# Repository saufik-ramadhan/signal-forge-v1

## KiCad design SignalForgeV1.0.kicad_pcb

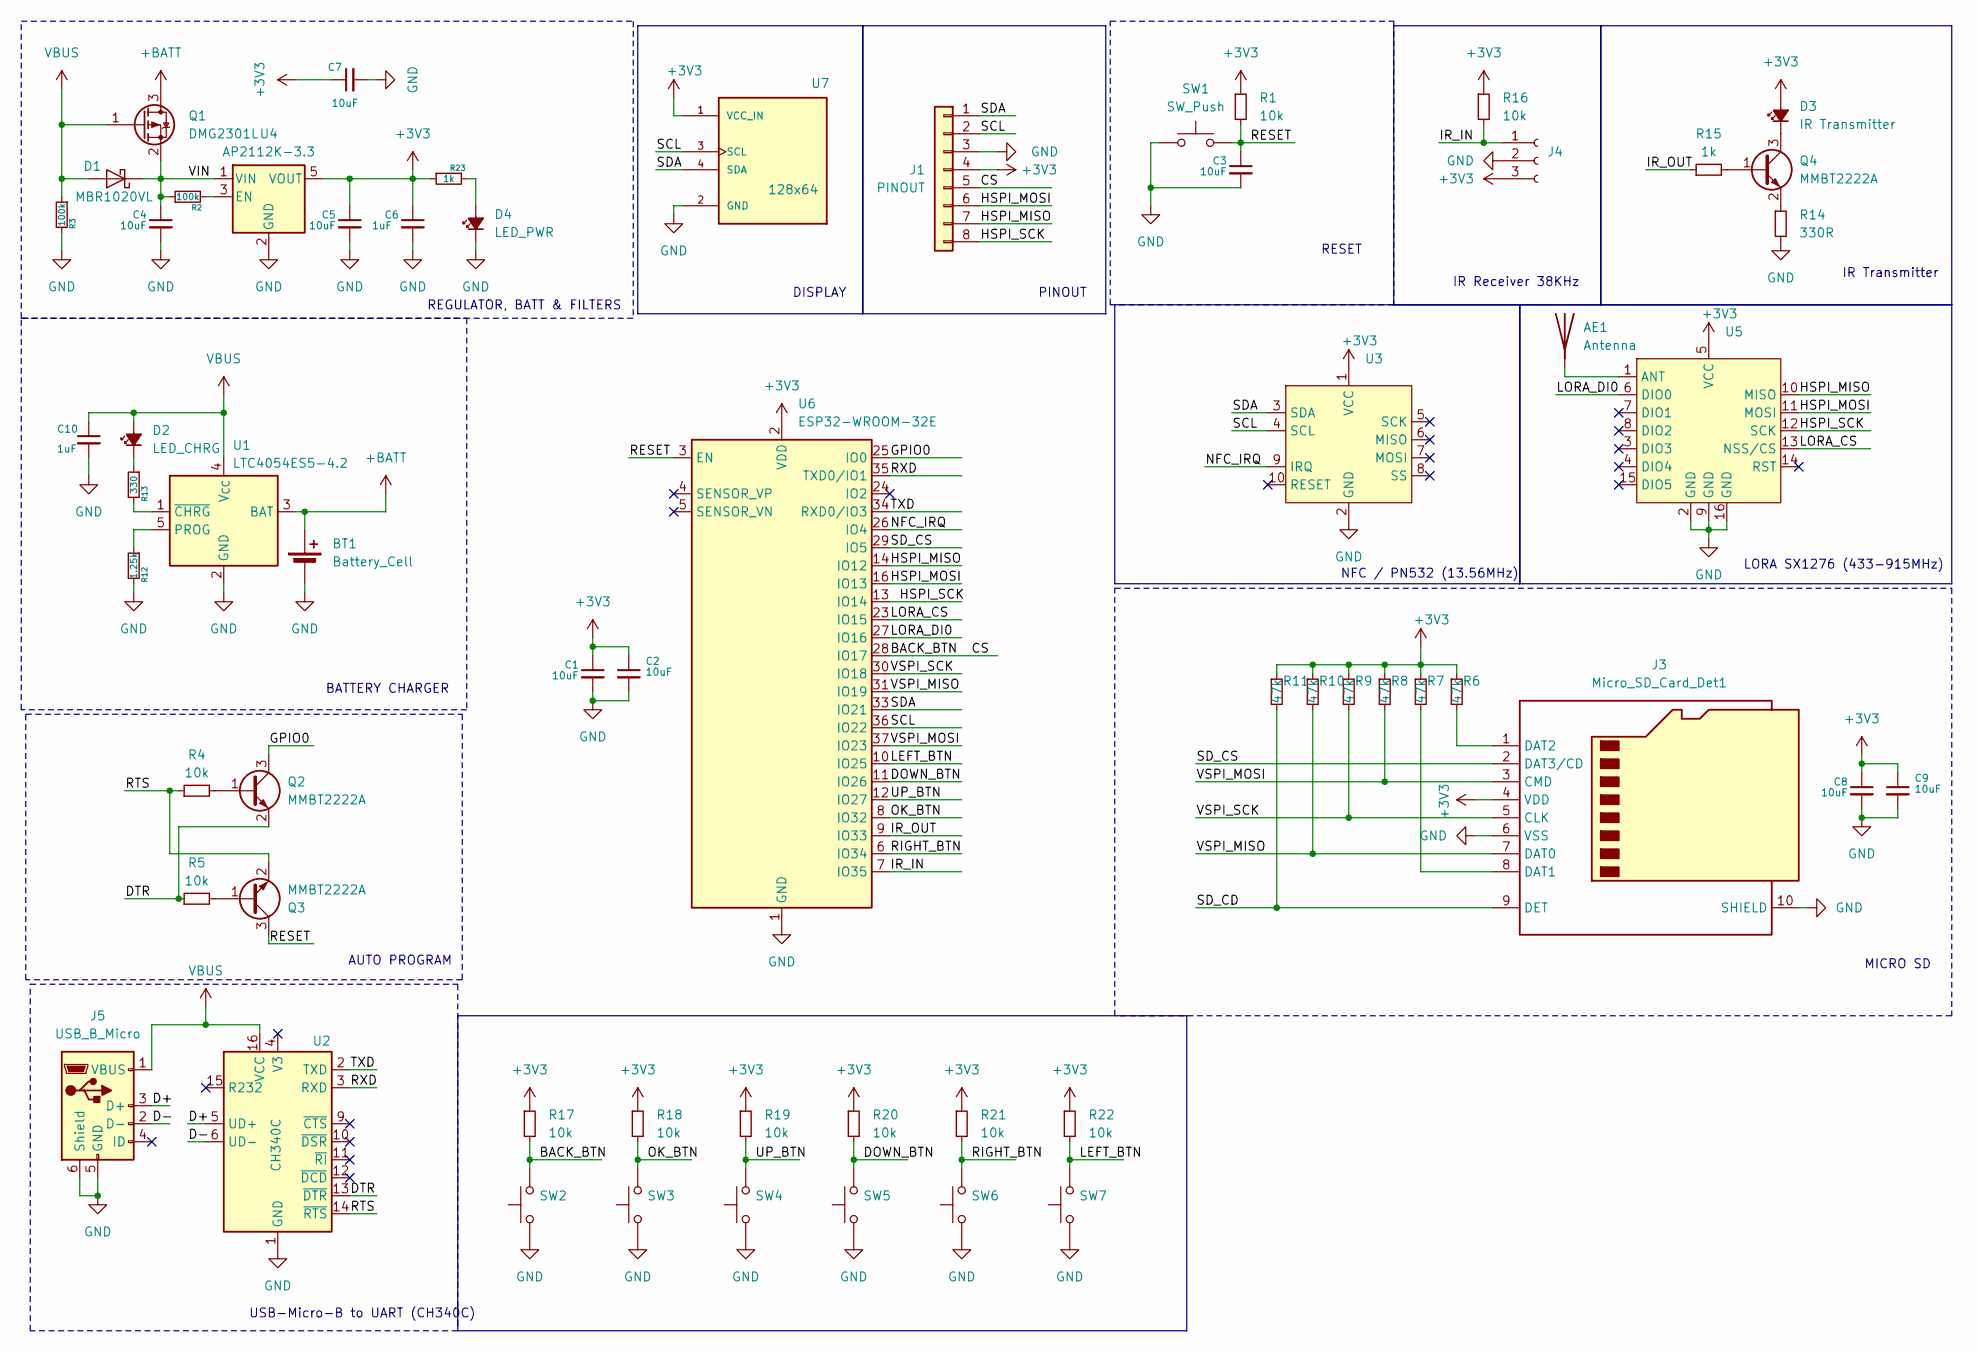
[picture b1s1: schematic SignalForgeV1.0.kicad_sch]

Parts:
AE1: Antenna; TestPoint_THTPad_D2.0mm_Drill1.0mm
BT1: Battery_Cell; JST_EH_S2B-EH_1x02_P2.50mm_Horizontal
C1, C2, C3, C4, C5, C7, C8, C9: 10uF; C_0805_2012Metric_Pad1.18x1.45mm_HandSolder
C6, C10: 1uF; C_0805_2012Metric_Pad1.18x1.45mm_HandSolder
D1: MBR1020VL; D_SOD-123F
D2: LED_CHRG; LED_0805_2012Metric_Pad1.15x1.40mm_HandSolder
D3: IR Transmitter; LED_D5.0mm_Horizontal_O1.27mm_Z3.0mm
D4: LED_PWR; LED_0805_2012Metric_Pad1.15x1.40mm_HandSolder
J1: PINOUT; PinSocket_1x08_P2.54mm_Horizontal
J3: Micro_SD_Card_Det1; J_SD_Card-micro_socket_A
J4: IR Receiver; PinHeader_1x03_P2.54mm_Vertical
J5: USB_B_Micro; USB_B_Micro_SMD-TE
Q1: DMG2301L; SOT-23
Q2, Q3, Q4: MMBT2222A; SOT-23
R1, R4, R5, R16, R17, R18, R19, R20, R21, R22: 10k; R_0805_2012Metric_Pad1.20x1.40mm_HandSolder
R2, R3: 100k; R_0805_2012Metric_Pad1.20x1.40mm_HandSolder
R6, R7, R8, R9, R10, R11: 47k; R_0805_2012Metric_Pad1.20x1.40mm_HandSolder
R12: 1.25k; R_0805_2012Metric_Pad1.20x1.40mm_HandSolder
R13: 330; R_0805_2012Metric_Pad1.20x1.40mm_HandSolder
R14: 330R; R_0805_2012Metric_Pad1.20x1.40mm_HandSolder
R15, R23: 1k; R_0805_2012Metric_Pad1.20x1.40mm_HandSolder
SW1: SW_Push; SW_SPST_EVQP7C
SW2: BACK_BTN; SW_SPST_TL3342
SW3: OK_BTN; SW_SPST_TL3342
SW4: UP_BTN; SW_SPST_TL3342
SW5: DOWN_BTN; SW_SPST_TL3342
SW6: RIGHT_BTN; SW_SPST_TL3342
SW7: LEFT_BTN; SW_SPST_TL3342
U1: LTC4054ES5-4.2; TSOT-23-5
U2: CH340C; SOIC-16_3.9x9.9mm_P1.27mm
U3: PN532_Module
U4: AP2112K-3.3; SOT-23-5_HandSoldering
U5: SX1276_Module
U6: ESP32-WROOM-32E
U7: 128x64; MODULE_DM-OLED096-636; PARTREV 2018-09-10

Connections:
+3V3: C1.1, C2.1, C5.1, C6.1, C7.1, C8.1, C9.1, D3.2 (A), J1.4, J3.4 (VDD), J4.3, R1.1, R6.1, R7.1, R8.1, R9.1, R10.1, R11.1, R16.1, R17.1, R18.1, R19.1, R20.1, R21.1, R22.1, R23.1, U3.1 (VCC), U4.5 (VOUT), U5.5 (VCC), U6.2 (VDD), U7.1 (VCC_IN)
+BATT: BT1.1 (+), Q1.3 (D), U1.3 (BAT)
/BACK_BTN: J1.5, R17.2, SW2.2, U6.28 (IO17)
/D+: J5.3 (D+), U2.5 (UD+)
/D-: J5.2 (D-), U2.6 (UD-)
/DOWN_BTN: R20.2, SW5.2, U6.11 (IO26)
/DTR: Q2.2 (E), R5.1, U2.13 (~DTR)
/GPIO0: Q2.3 (C), U6.25 (IO0)
/HSPI_MISO: J1.7, U5.10 (MISO), U6.14 (IO12)
/HSPI_MOSI: J1.6, U5.11 (MOSI), U6.16 (IO13)
/HSPI_SCK: J1.8, U5.12 (SCK), U6.13 (IO14)
/IR_IN: J4.1, R16.2, U6.7 (IO35)
/IR_OUT: R15.1, U6.9 (IO33)
/LEFT_BTN: R22.2, SW7.2, U6.10 (IO25)
/LORA_CS: U5.13 (NSS/CS), U6.23 (IO15)
/LORA_DI0: U5.6 (DIO0), U6.27 (IO16)
/NFC_IRQ: U3.9 (IRQ), U6.26 (IO4)
/OK_BTN: R18.2, SW3.2, U6.8 (IO32)
/RESET: C3.1, Q3.3 (C), R1.2, SW1.2, U6.3 (EN)
/RIGHT_BTN: R21.2, SW6.2, U6.6 (IO34)
/RTS: Q3.2 (E), R4.1, U2.14 (~RTS)
/RXD: U2.3 (RXD), U6.35 (TXD0/IO1)
/SCL: J1.2, U3.4 (SCL), U6.36 (IO22), U7.3 (SCL)
/SDA: J1.1, U3.3 (SDA), U6.33 (IO21), U7.4 (SDA)
/SD_CD: J3.9 (DET), R11.2
/SD_CS: J3.2 (DAT3/CD), U6.29 (IO5)
/TXD: U2.2 (TXD), U6.34 (RXD0/IO3)
/UP_BTN: R19.2, SW4.2, U6.12 (IO27)
/VIN: C4.1, D1.1 (K), Q1.2 (S), R2.1, U4.1 (VIN)
/VSPI_MISO: J3.7 (DAT0), R10.2, U6.31 (IO19)
/VSPI_MOSI: J3.3 (CMD), R8.2, U6.37 (IO23)
/VSPI_SCK: J3.5 (CLK), R9.2, U6.30 (IO18)
GND: BT1.2 (-), C1.2, C2.2, C3.2, C4.2, C5.2, C6.2, C7.2, C8.2, C9.2, C10.2, D4.1 (K), J1.3, J3.6 (VSS), J3.10 (SHIELD), J4.2, J5.5 (GND), J5.6 (Shield), R3.2, R12.2, R14.2, SW1.1, SW2.1, SW3.1, SW4.1, SW5.1, SW6.1, SW7.1, U1.2 (GND), U2.1 (GND), U3.2 (GND), U4.2 (GND), U5.2 (GND), U5.9 (GND), U5.16 (GND), U6.1 (GND), U6.15 (GND), U6.38 (GND), U6.39 (GND), U7.2 (GND)
unnamed: AE1.1 (A), U5.1 (ANT)
unnamed: D2.1 (K), R13.1
unnamed: D3.1 (K), Q4.3 (C)
unnamed: D4.2 (A), R23.2
unnamed: J3.8 (DAT1), R7.2
unnamed: J3.1 (DAT2), R6.2
unnamed: Q2.1 (B), R4.2
unnamed: Q3.1 (B), R5.2
unnamed: Q4.1 (B), R15.2
unnamed: Q4.2 (E), R14.1
unnamed: R12.1, U1.5 (PROG)
unnamed: R13.2, U1.1 (~CHRG)
unnamed: R2.2, U4.3 (EN)
VBUS: C10.1, D1.2 (A), D2.2 (A), J5.1 (VBUS), Q1.1 (G), R3.1, U1.4 (V_{CC}), U2.16 (VCC)

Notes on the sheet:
NFC / PN532 (13.56MHz)
RESET
PINOUT
AUTO PROGRAM
BATTERY CHARGER
LORA SX1276 (433-915MHz)
IR Transmitter
USB-Micro-B to UART (CH340C)
IR Receiver 38KHz
REGULATOR, BATT & FILTERS
MICRO SD
DISPLAY

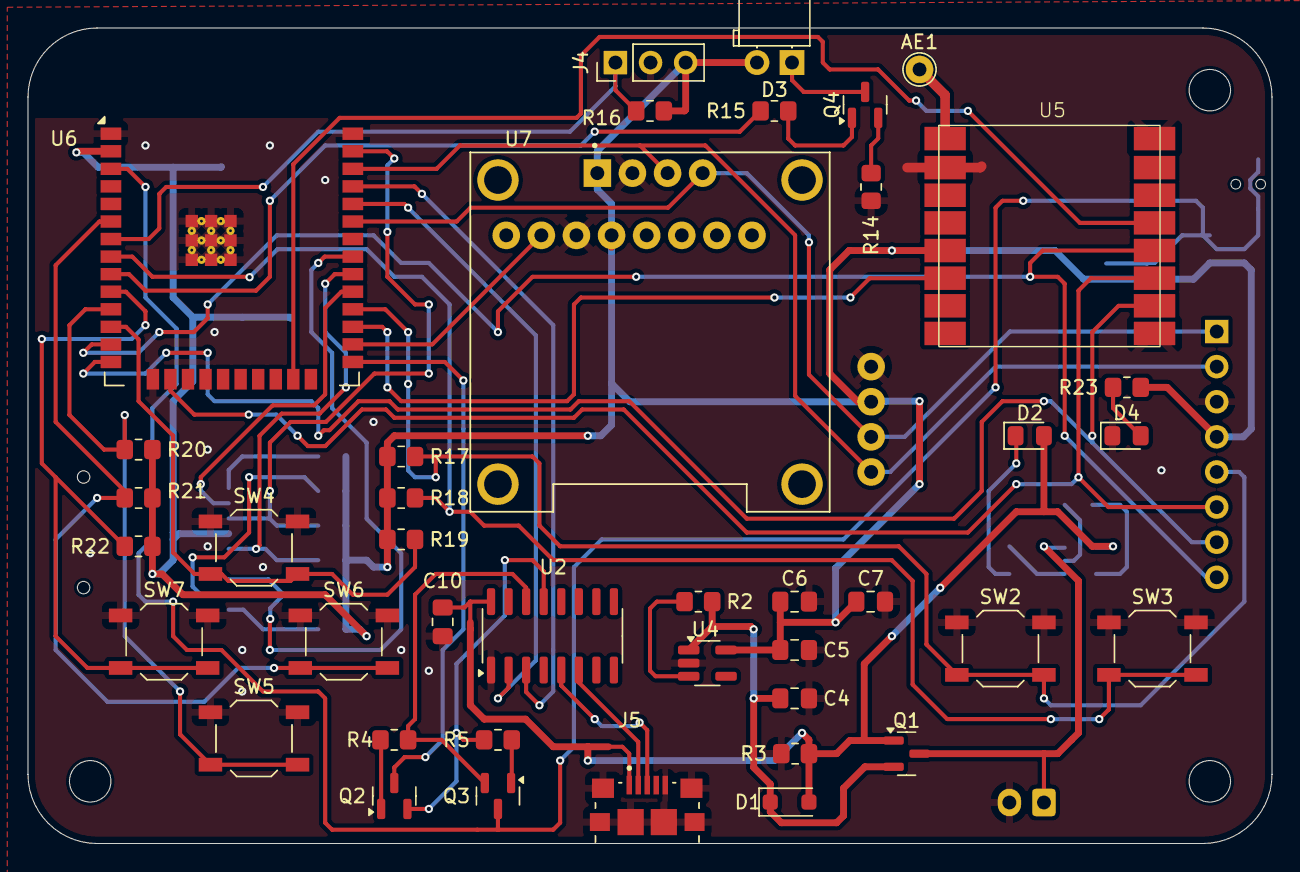
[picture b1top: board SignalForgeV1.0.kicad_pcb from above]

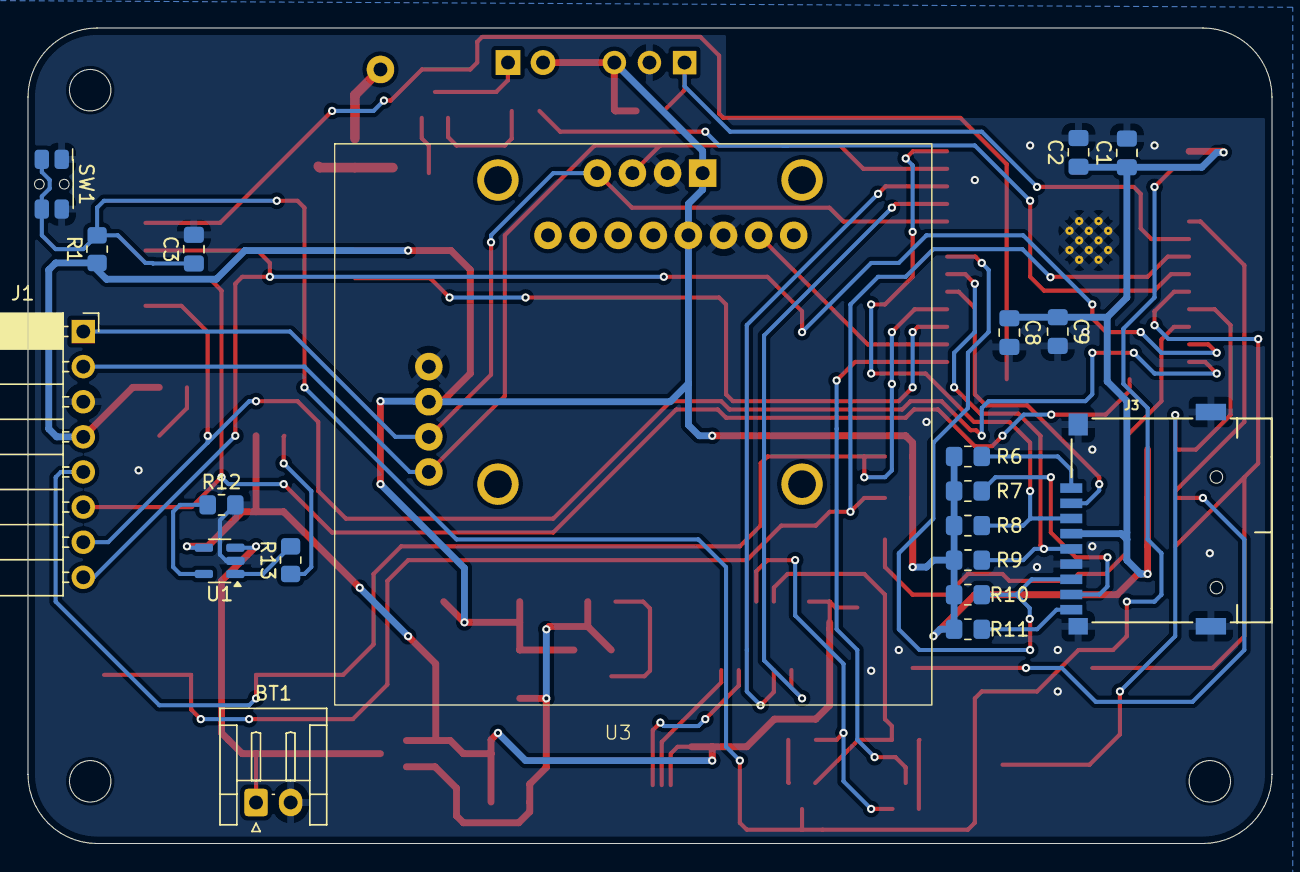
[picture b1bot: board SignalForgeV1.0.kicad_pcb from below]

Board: 2 copper layers, 90.0 x 59.0 mm, 61 parts (20 on the bottom side), 47 nets.

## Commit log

2025-01-08 SignalForgeV1.0
2025-01-12 feat: pcb design and 3d
